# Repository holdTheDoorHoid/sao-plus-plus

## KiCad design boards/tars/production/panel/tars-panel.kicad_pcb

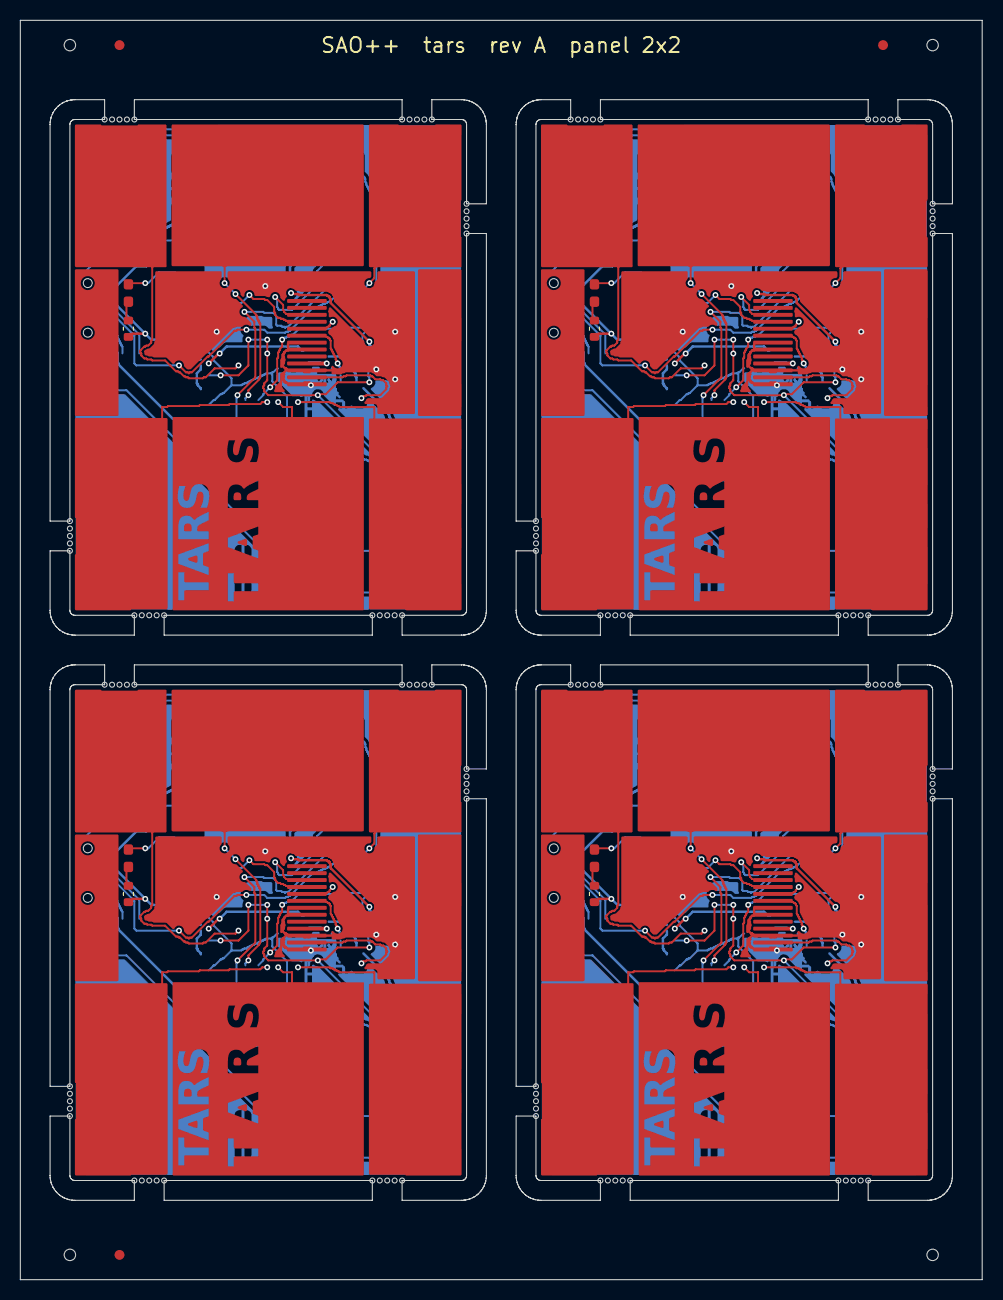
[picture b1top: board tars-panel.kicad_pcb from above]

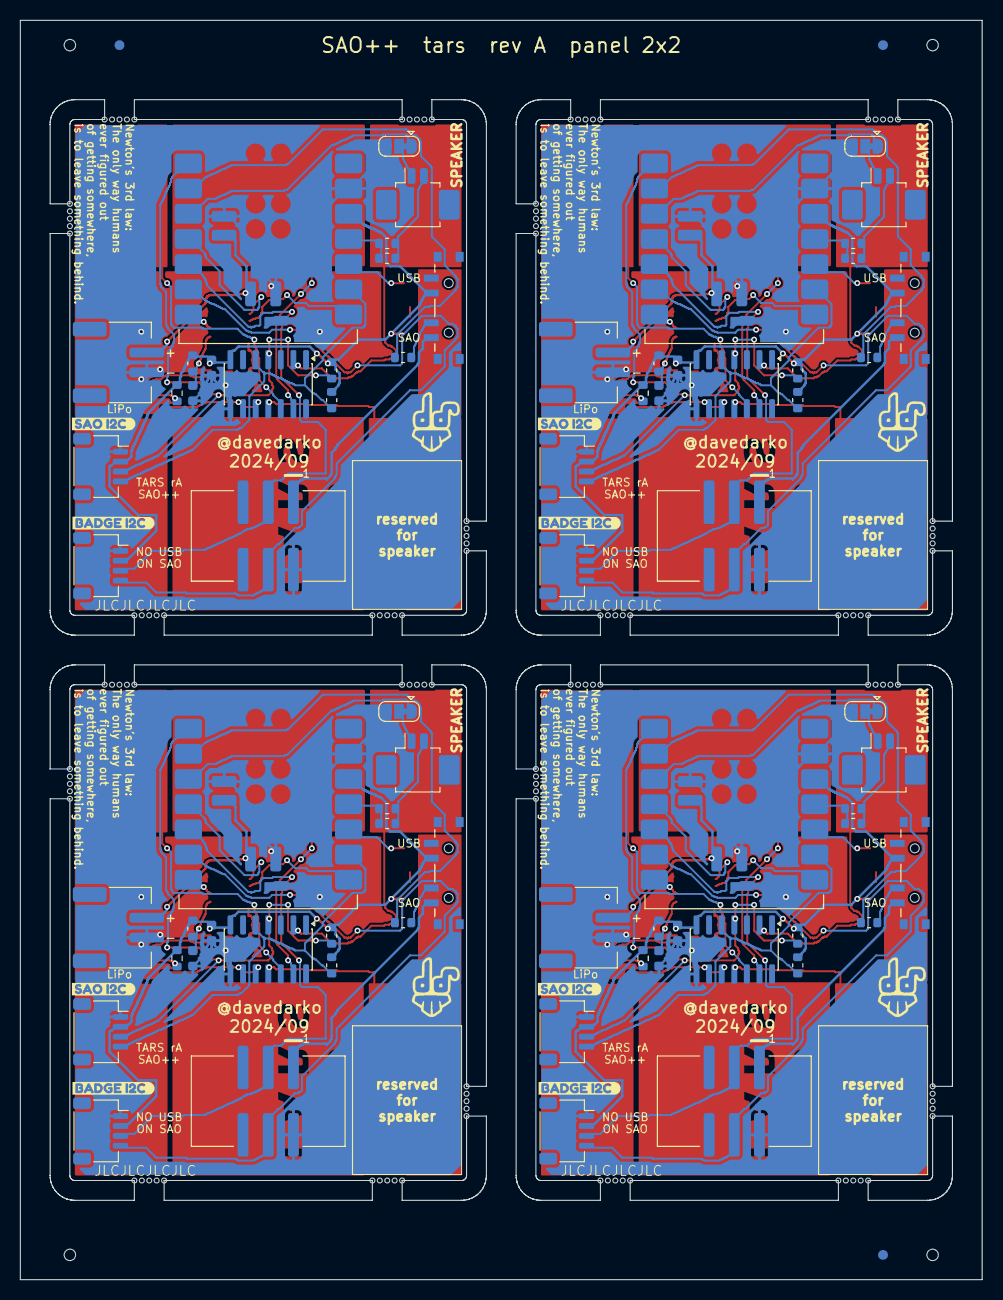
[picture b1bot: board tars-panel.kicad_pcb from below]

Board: 2 copper layers, 97.0 x 127.0 mm, 120 parts (84 on the bottom side), 108 nets.

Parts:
C101, C102, C201, C202, C301, C302, C401, C402: 100n; SAOPP_C_0603_1608Metric
D101, D201, D301, D401: red; LED_0603_1608Metric_Pad1.05x0.95mm_HandSolder
J101, J201, J301, J401: SAO v1.69bis; SAOPP_CONN-01_BoxHeader_2x03_P2.54mm_SMD_XFCN_BH254VS-6P
J102, J202, J302, J402: speaker; Molex_PicoBlade_53261-0271_1x02-1MP_P1.25mm_Horizontal
J103, J203, J303, J403: Qwiic: badge I2C; JST_SH_SM04B-SRSS-TB_1x04-1MP_P1.00mm_Horizontal
J104, J204, J304, J404: Qwiic: XIAO's own I2C; JST_SH_SM04B-SRSS-TB_1x04-1MP_P1.00mm_Horizontal
J105, J205, J305, J405: LiPo 3.7 V; SAOPP_CONN-10_JST_PH_S2B-PH-SM4-TB_1x02_Horizontal
JP101, JP201, JP301, JP401: speaker mode; SolderJumper-3_P1.3mm_Bridged12_RoundedPad1.0x1.5mm
R109, R209, R309, R409: 11; R_0603_1608Metric
R110, R111, R112, R116, R210, R211, R212, R216, R310, R311, R312, R316, R410, R411, R412, R416: 1.3k; SAOPP_R_0603_1608Metric
R113, R114, R115, R213, R214, R215, R313, R314, R315, R413, R414, R415: 330; SAOPP_R_0603_1608Metric
Ref**: Val**; davedarko_logo_silk_outline
Ref**#2, Ref**#3, Ref**#4: Val**; davedarko_logo_silk_outline
SW101, SW201, SW301, SW401: SAO / OFF / USB-BAT; SAOPP_SW-01_Slide_SP3T_CK_PCM13SMTR
TP101, TP201, TP301, TP401: touch A; TestPoint_Pad_D1.0mm
TP102, TP202, TP302, TP402: touch up; TestPoint_Pad_D1.0mm
TP103, TP203, TP303, TP403: touch B; TestPoint_Pad_D1.0mm
TP104, TP204, TP304, TP404: touch left; TestPoint_Pad_D1.0mm
TP105, TP205, TP305, TP405: touch down; TestPoint_Pad_D1.0mm
TP106, TP206, TP306, TP406: touch right; TestPoint_Pad_D1.0mm
U101, U201, U301, U401: ST7735S 80x160; ST7735S-160x80-13PIN
U102, U202, U302, U402: XIAO ESP32-C3 / S3 / C6; SAOPP_MCU-01_Seeed_XIAO_SMD_C3_S3_C6
U103, U203, U303, U403: CAP1206-1; SOIC-14_3.9x8.7mm_P1.27mm
kibuzzard-66F128E4, kibuzzard-66F128E4#2, kibuzzard-66F128E4#3, kibuzzard-66F128E4#4: G***; kibuzzard-66F128E4
kibuzzard-66F12846, kibuzzard-66F12846#2, kibuzzard-66F12846#3, kibuzzard-66F12846#4: G***; kibuzzard-66F12846

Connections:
B2-BAT+: J205.1, U202.15
B2-GND: C201.2, C202.2, J201.2, J203.1, J204.1, J205.2, JP201.3, U201.7, U201.8, U201.11, U201.13, U202.13, U202.16, U203.8
B2-LEDA: R209.2, U201.12
B2-LED_A: D201.2, R210.2
B2-LED_K: D201.1, U202.10
B2-OFF_SENSE: R213.2, U202.2
B2-OFF_SW: R213.1, SW201.2
B2-PRIV_SCL: J204.4, R212.2, U202.9, U203.5
B2-PRIV_SDA: J204.3, R211.2, U202.1, U203.4
B2-SCL: J201.4, J203.4, U202.6
B2-SDA: J201.3, J203.3, U202.5
B2-SPK_1: J202.1, JP201.2
B2-SPK_A: R214.1, R215.1, U202.11
B2-SPK_AR: J202.2, R214.2, R215.2
B2-SPK_B: JP201.1, U202.3
B2-TFT_DC: U201.5, U202.7
B2-TFT_MOSI: U201.3, U202.4
B2-TFT_RST: C201.1, R216.2, U201.6
B2-TFT_SCLK: U201.4, U202.8
B2-TOUCH_A: TP201.1, U203.2
B2-TOUCH_B: TP203.1, U203.12
B2-TOUCH_DOWN: TP205.1, U203.10
B2-TOUCH_LEFT: TP204.1, U203.11
B2-TOUCH_RIGHT: TP206.1, U203.9
B2-TOUCH_UP: TP202.1, U203.13
B2-V3V3: C202.1, J203.2, J204.2, R209.1, R210.1, R211.1, R212.1, R216.1, SW201.3, U201.10, U202.12, U203.7
B2-VSAO: J201.1, SW201.1
B3-BAT+: J305.1, U302.15
B3-GND: C301.2, C302.2, J301.2, J303.1, J304.1, J305.2, JP301.3, U301.7, U301.8, U301.11, U301.13, U302.13, U302.16, U303.8
B3-LEDA: R309.2, U301.12
B3-LED_A: D301.2, R310.2
B3-LED_K: D301.1, U302.10
B3-OFF_SENSE: R313.2, U302.2
B3-OFF_SW: R313.1, SW301.2
B3-PRIV_SCL: J304.4, R312.2, U302.9, U303.5
B3-PRIV_SDA: J304.3, R311.2, U302.1, U303.4
B3-SCL: J301.4, J303.4, U302.6
B3-SDA: J301.3, J303.3, U302.5
B3-SPK_1: J302.1, JP301.2
B3-SPK_A: R314.1, R315.1, U302.11
B3-SPK_AR: J302.2, R314.2, R315.2
B3-SPK_B: JP301.1, U302.3
B3-TFT_DC: U301.5, U302.7
B3-TFT_MOSI: U301.3, U302.4
B3-TFT_RST: C301.1, R316.2, U301.6
B3-TFT_SCLK: U301.4, U302.8
B3-TOUCH_A: TP301.1, U303.2
B3-TOUCH_B: TP303.1, U303.12
B3-TOUCH_DOWN: TP305.1, U303.10
B3-TOUCH_LEFT: TP304.1, U303.11
B3-TOUCH_RIGHT: TP306.1, U303.9
B3-TOUCH_UP: TP302.1, U303.13
B3-V3V3: C302.1, J303.2, J304.2, R309.1, R310.1, R311.1, R312.1, R316.1, SW301.3, U301.10, U302.12, U303.7
B3-VSAO: J301.1, SW301.1
B4-BAT+: J405.1, U402.15
B4-GND: C401.2, C402.2, J401.2, J403.1, J404.1, J405.2, JP401.3, U401.7, U401.8, U401.11, U401.13, U402.13, U402.16, U403.8
B4-LEDA: R409.2, U401.12
B4-LED_A: D401.2, R410.2
B4-LED_K: D401.1, U402.10
B4-OFF_SENSE: R413.2, U402.2
B4-OFF_SW: R413.1, SW401.2
B4-PRIV_SCL: J404.4, R412.2, U402.9, U403.5
B4-PRIV_SDA: J404.3, R411.2, U402.1, U403.4
B4-SCL: J401.4, J403.4, U402.6
B4-SDA: J401.3, J403.3, U402.5
B4-SPK_1: J402.1, JP401.2
B4-SPK_A: R414.1, R415.1, U402.11
B4-SPK_AR: J402.2, R414.2, R415.2
B4-SPK_B: JP401.1, U402.3
B4-TFT_DC: U401.5, U402.7
B4-TFT_MOSI: U401.3, U402.4
B4-TFT_RST: C401.1, R416.2, U401.6
B4-TFT_SCLK: U401.4, U402.8
B4-TOUCH_A: TP401.1, U403.2
B4-TOUCH_B: TP403.1, U403.12
B4-TOUCH_DOWN: TP405.1, U403.10
B4-TOUCH_LEFT: TP404.1, U403.11
B4-TOUCH_RIGHT: TP406.1, U403.9
B4-TOUCH_UP: TP402.1, U403.13
B4-V3V3: C402.1, J403.2, J404.2, R409.1, R410.1, R411.1, R412.1, R416.1, SW401.3, U401.10, U402.12, U403.7
B4-VSAO: J401.1, SW401.1
BAT+: J105.1, U102.15
GND: C101.2, C102.2, J101.2, J103.1, J104.1, J105.2, JP101.3, U101.7, U101.8, U101.11, U101.13, U102.13, U102.16, U103.8
LEDA: R109.2, U101.12
LED_A: D101.2, R110.2
LED_K: D101.1, U102.10
OFF_SENSE: R113.2, U102.2
OFF_SW: R113.1, SW101.2
PRIV_SCL: J104.4, R112.2, U102.9, U103.5
PRIV_SDA: J104.3, R111.2, U102.1, U103.4
SCL: J101.4, J103.4, U102.6
SDA: J101.3, J103.3, U102.5
SPK_1: J102.1, JP101.2
SPK_A: R114.1, R115.1, U102.11
SPK_AR: J102.2, R114.2, R115.2
SPK_B: JP101.1, U102.3
TFT_DC: U101.5, U102.7
TFT_MOSI: U101.3, U102.4
TFT_RST: C101.1, R116.2, U101.6
TFT_SCLK: U101.4, U102.8
TOUCH_A: TP101.1, U103.2
TOUCH_B: TP103.1, U103.12
TOUCH_DOWN: TP105.1, U103.10
TOUCH_LEFT: TP104.1, U103.11
TOUCH_RIGHT: TP106.1, U103.9
TOUCH_UP: TP102.1, U103.13
V3V3: C102.1, J103.2, J104.2, R109.1, R110.1, R111.1, R112.1, R116.1, SW101.3, U101.10, U102.12, U103.7
VSAO: J101.1, SW101.1

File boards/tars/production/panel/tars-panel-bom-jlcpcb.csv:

Comment,Designator,Footprint,LCSC Part #
100n,"C101,C102,C201,C202,C301,C302,C401,C402",SAOPP_C_0603_1608Metric,C14663
red,"D101,D201,D301,D401",LED_0603_1608Metric_Pad1.05x0.95mm_HandSolder,C125099
SAO v1.69bis,"J101,J201,J301,J401",SAOPP_CONN-01_BoxHeader_2x03_P2.54mm_SMD_XFCN_BH254VS-6P,C492445
speaker,"J102,J202,J302,J402",Molex_PicoBlade_53261-0271_1x02-1MP_P1.25mm_Horizontal,C177225
Qwiic: badge I2C,"J103,J203,J303,J403",JST_SH_SM04B-SRSS-TB_1x04-1MP_P1.00mm_Horizontal,C160404
Qwiic: XIAO's own I2C,"J104,J204,J304,J404",JST_SH_SM04B-SRSS-TB_1x04-1MP_P1.00mm_Horizontal,C160404
LiPo 3.7 V,"J105,J205,J305,J405",SAOPP_CONN-10_JST_PH_S2B-PH-SM4-TB_1x02_Horizontal,C295747
11,"R109,R209,R309,R409",R_0603_1608Metric,
1.3k,"R111,R112,R116,R211,R212,R216,R311,R312,R316,R411,R412,R416,R110,R210,R310,R410",SAOPP_R_0603_1608Metric,C22767
330,"R113,R114,R115,R213,R214,R215,R313,R314,R315,R413,R414,R415",SAOPP_R_0603_1608Metric,C23138
SAO / OFF / USB-BAT,"SW101,SW201,SW301,SW401",SAOPP_SW-01_Slide_SP3T_CK_PCM13SMTR,C221842
ST7735S 80x160,"U101,U201,U301,U401",ST7735S-160x80-13PIN,
XIAO ESP32-C3 / S3 / C6,"U102,U202,U302,U402",SAOPP_MCU-01_Seeed_XIAO_SMD_C3_S3_C6,
CAP1206-1,"U103,U203,U303,U403",SOIC-14_3.9x8.7mm_P1.27mm,C2652106

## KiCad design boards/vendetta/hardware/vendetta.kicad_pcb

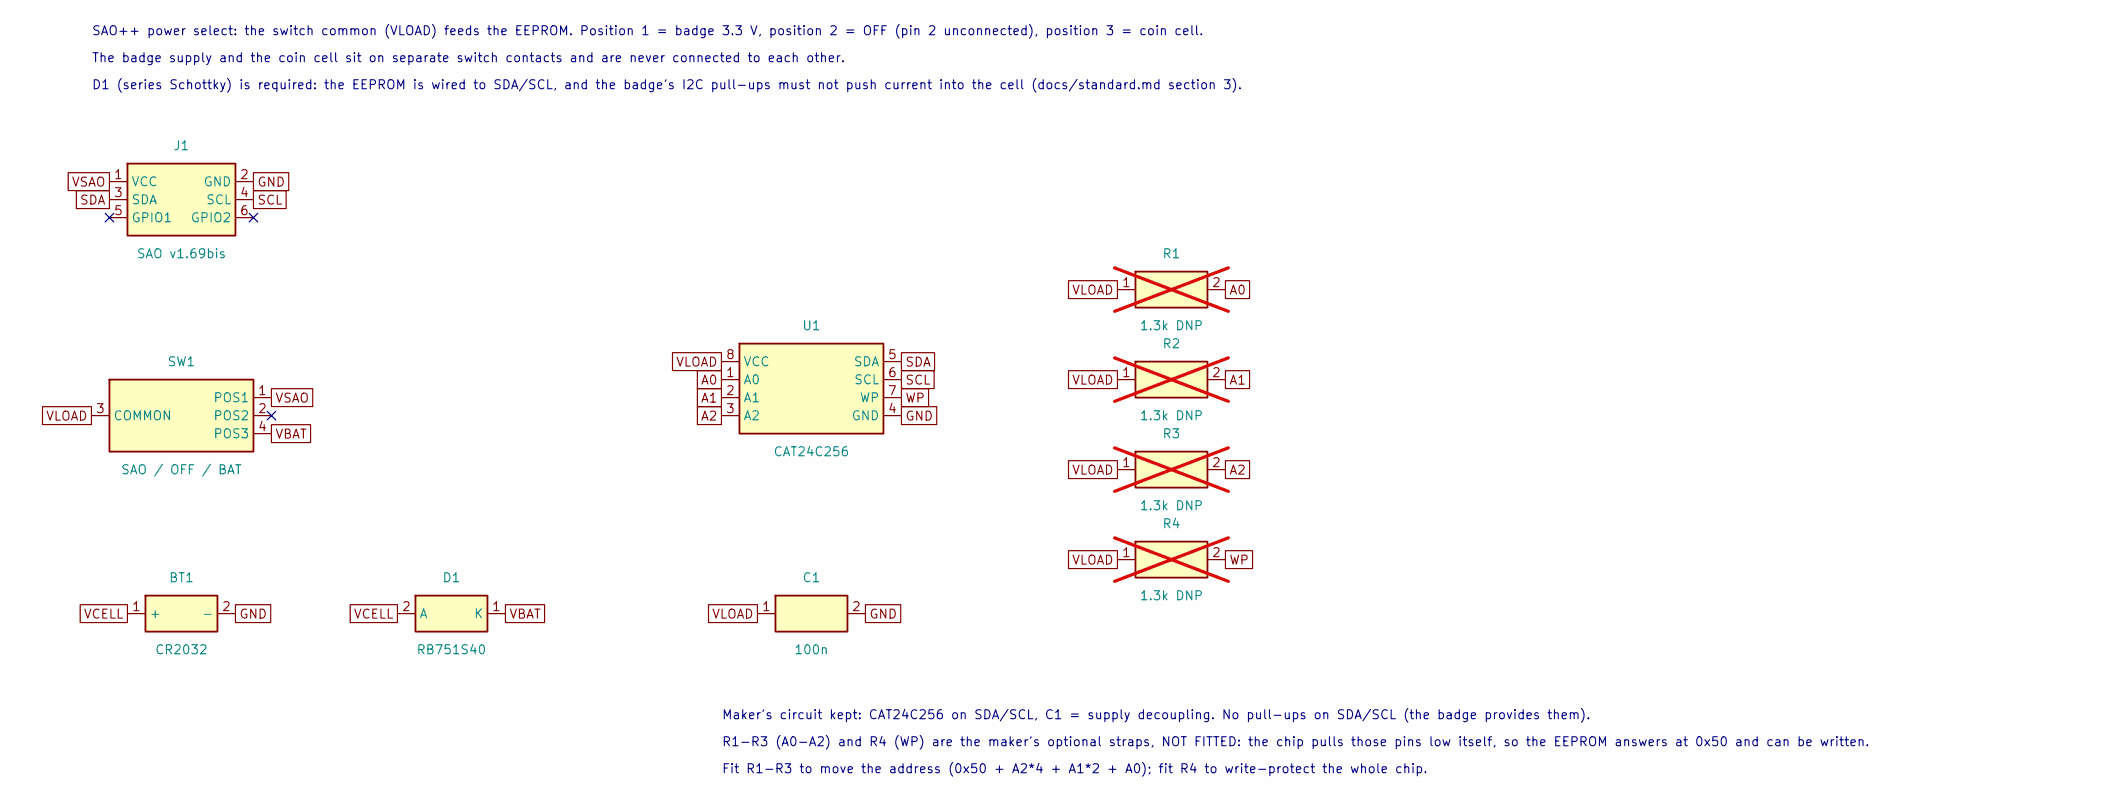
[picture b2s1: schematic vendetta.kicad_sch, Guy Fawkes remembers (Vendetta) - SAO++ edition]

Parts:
BT1: CR2032; SAOPP_BAT-01_CR2032_SMD_TE_BAT-HLD-001; MPN BAT-HLD-001; LCSC C7501066
C1: 100n; SAOPP_C_0603_1608Metric; MPN CC0603KRX7R9BB104; LCSC C14663
D1: RB751S40; D_SOD-523; MPN RB751S40T1G; LCSC C232576
J1: SAO v1.69bis; SAOPP_CONN-01_BoxHeader_2x03_P2.54mm_SMD_XFCN_BH254VS-6P; MPN BH254VS-6P; LCSC C492445
R1, R2, R3, R4: 1.3k DNP; SAOPP_R_0603_1608Metric; MPN 0603WAF1301T5E; LCSC C22767; not fitted
SW1: SAO / OFF / BAT; SAOPP_SW-01_Slide_SP3T_CK_PCM13SMTR; MPN PCM13SMTR; LCSC C221842
U1: CAT24C256; SOIC-8_5.3x5.3mm_P1.27mm; MPN CAT24C256XI-T2

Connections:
A0: R1.2, U1.1 (A0)
A1: R2.2, U1.2 (A1)
A2: R3.2, U1.3 (A2)
GND: BT1.2 (-), C1.2, J1.2 (GND), U1.4 (GND)
SCL: J1.4 (SCL), U1.6 (SCL)
SDA: J1.3 (SDA), U1.5 (SDA)
VBAT: D1.1 (K), SW1.4 (POS3)
VCELL: BT1.1 (+), D1.2 (A)
VLOAD: C1.1, R1.1, R2.1, R3.1, R4.1, SW1.3 (COMMON), U1.8 (VCC)
VSAO: J1.1 (VCC), SW1.1 (POS1)
WP: R4.2, U1.7 (WP)

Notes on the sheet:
SAO++ power select: the switch common (VLOAD) feeds the EEPROM. Position 1 = badge 3.3 V, position 2 = OFF (pin 2 unconnected), position 3 = coin cell.
The badge supply and the coin cell sit on separate switch contacts and are never connected to each other.
D1 (series Schottky) is required: the EEPROM is wired to SDA/SCL, and the badge's I2C pull-ups must not push current into the cell (docs/standard.md section 3).
Maker's circuit kept: CAT24C256 on SDA/SCL, C1 = supply decoupling. No pull-ups on SDA/SCL (the badge provides them).
R1-R3 (A0-A2) and R4 (WP) are the maker's optional straps, NOT FITTED: the chip pulls those pins low itself, so the EEPROM answers at 0x50 and can be written.
Fit R1-R3 to move the address (0x50 + A2*4 + A1*2 + A0); fit R4 to write-protect the whole chip.

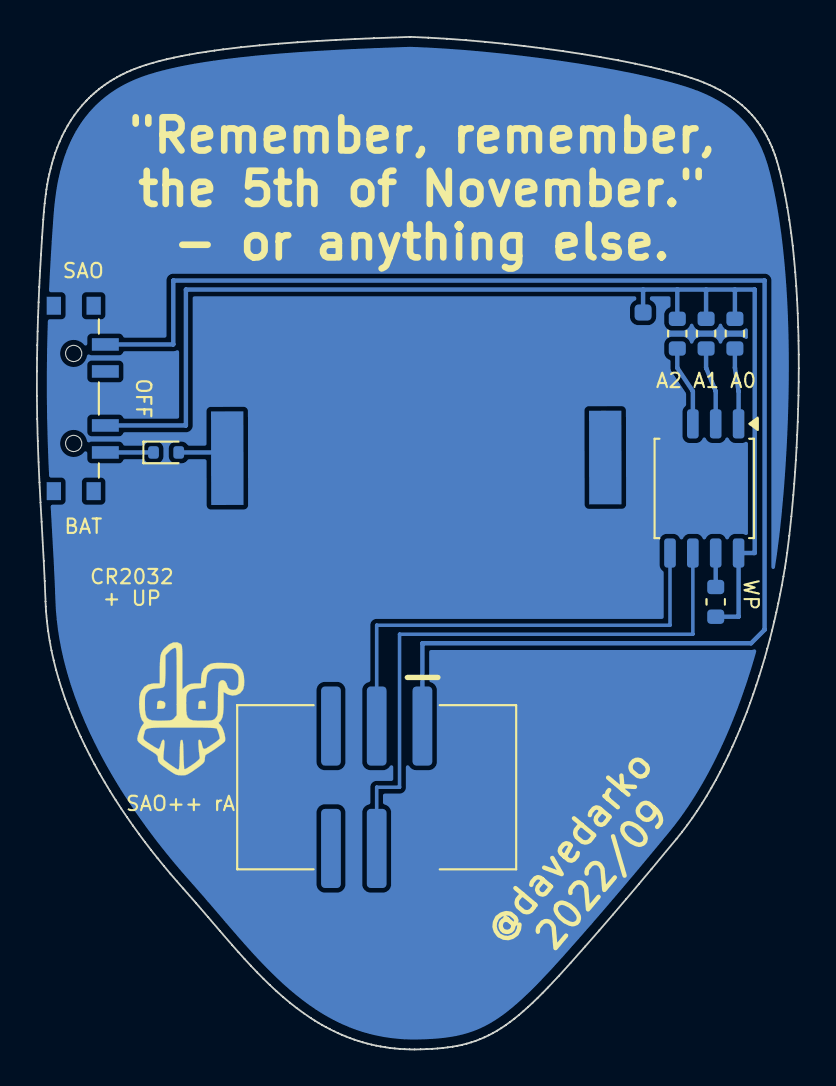
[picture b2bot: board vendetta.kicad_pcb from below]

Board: 2 copper layers, 42.3 x 56.3 mm, 12 parts (11 on the bottom side), 11 nets.

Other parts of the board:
Ref**: Val**; vendettaSAO
Ref**#2: Val**; davedarko_logo_silk_outline

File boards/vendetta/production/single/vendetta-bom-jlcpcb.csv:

Comment,Designator,Footprint,LCSC Part #
CR2032,BT1,SAOPP_BAT-01_CR2032_SMD_TE_BAT-HLD-001,C7501066
100n,C1,SAOPP_C_0603_1608Metric,C14663
RB751S40,D1,D_SOD-523,C232576
SAO v1.69bis,J1,SAOPP_CONN-01_BoxHeader_2x03_P2.54mm_SMD_XFCN_BH254VS-6P,C492445
SAO / OFF / BAT,SW1,SAOPP_SW-01_Slide_SP3T_CK_PCM13SMTR,C221842
CAT24C256,U1,SOIC-8_5.3x5.3mm_P1.27mm,

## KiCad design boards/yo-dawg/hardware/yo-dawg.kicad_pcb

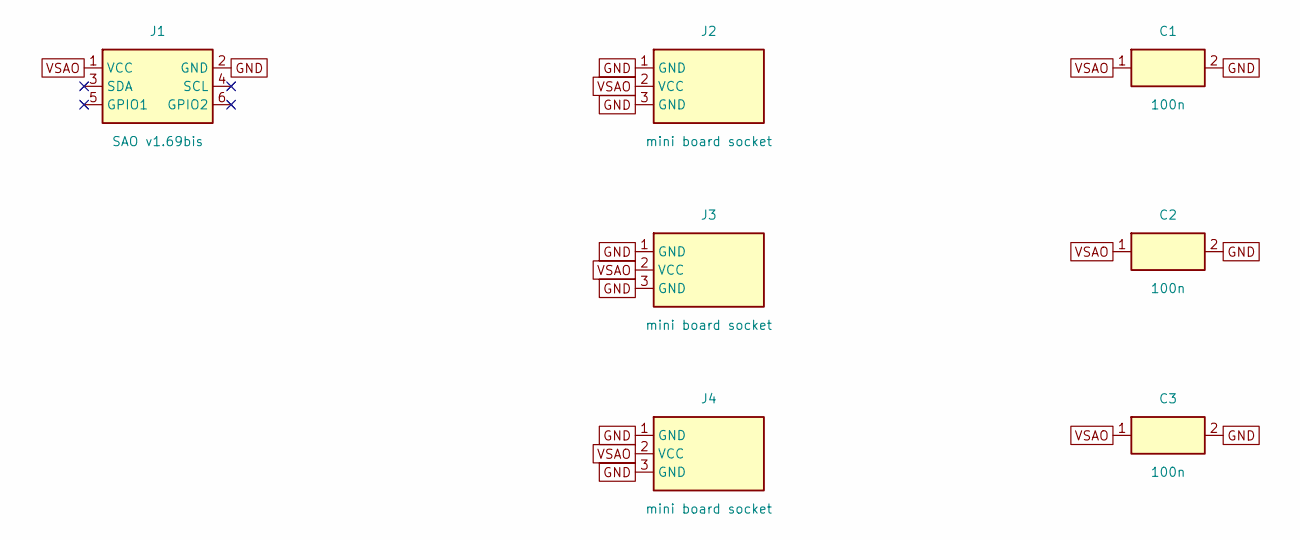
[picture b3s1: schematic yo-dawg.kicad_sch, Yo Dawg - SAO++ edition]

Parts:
C1, C2, C3: 100n; SAOPP_C_0603_1608Metric; MPN CC0603KRX7R9BB104; LCSC C14663
J1: SAO v1.69bis; SAOPP_CONN-01_BoxHeader_2x03_P2.54mm_SMD_XFCN_BH254VS-6P; MPN BH254VS-6P; LCSC C492445
J2, J3, J4: mini board socket; PinSocket_1x03_P1.27mm_Vertical; MPN not chosen: 1x3 female socket strip, 1.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

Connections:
GND: C1.2, C2.2, C3.2, J1.2 (GND), J2.1 (GND), J2.3 (GND), J3.1 (GND), J3.3 (GND), J4.1 (GND), J4.3 (GND)
VSAO: C1.1, C2.1, C3.1, J1.1 (VCC), J2.2 (VCC), J3.2 (VCC), J4.2 (VCC)

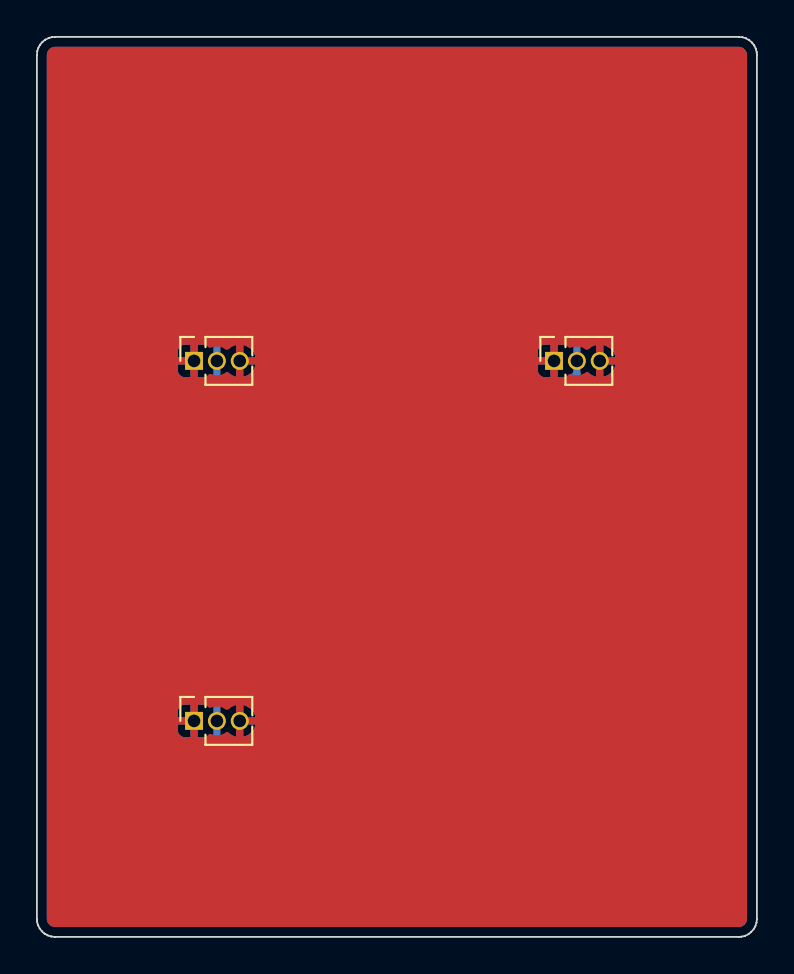
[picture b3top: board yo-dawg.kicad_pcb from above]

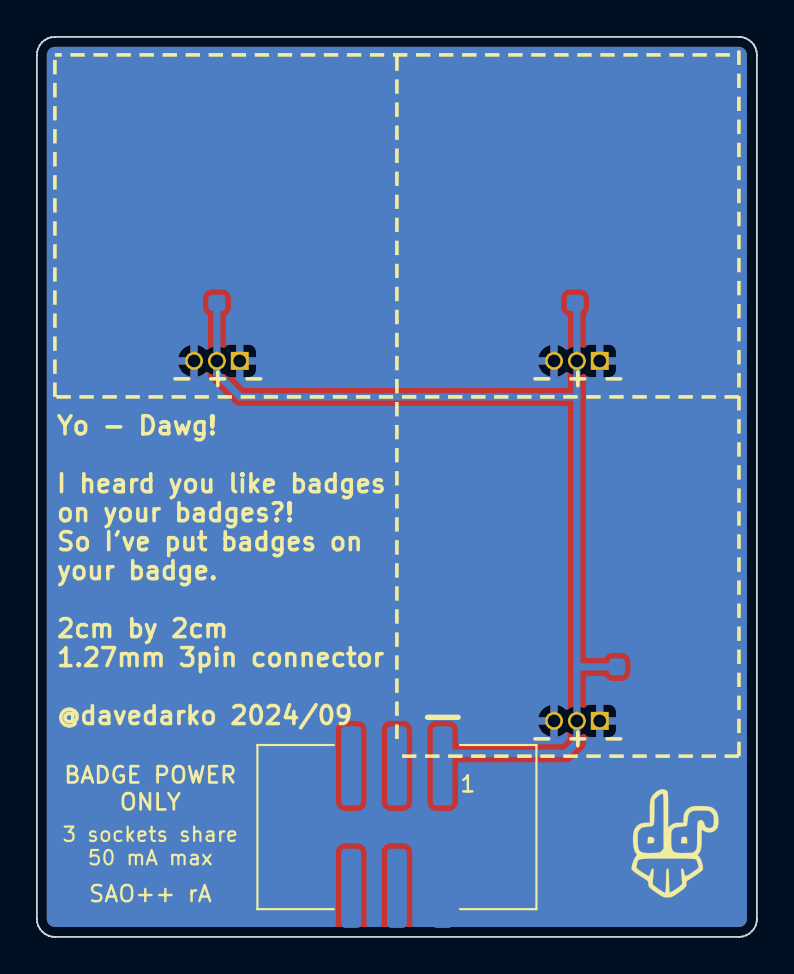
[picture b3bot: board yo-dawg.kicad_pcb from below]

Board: 2 copper layers, 40.0 x 50.0 mm, 8 parts (5 on the bottom side), 2 nets.

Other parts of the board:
Ref**: Val**; davedarko_logo_silk_outline

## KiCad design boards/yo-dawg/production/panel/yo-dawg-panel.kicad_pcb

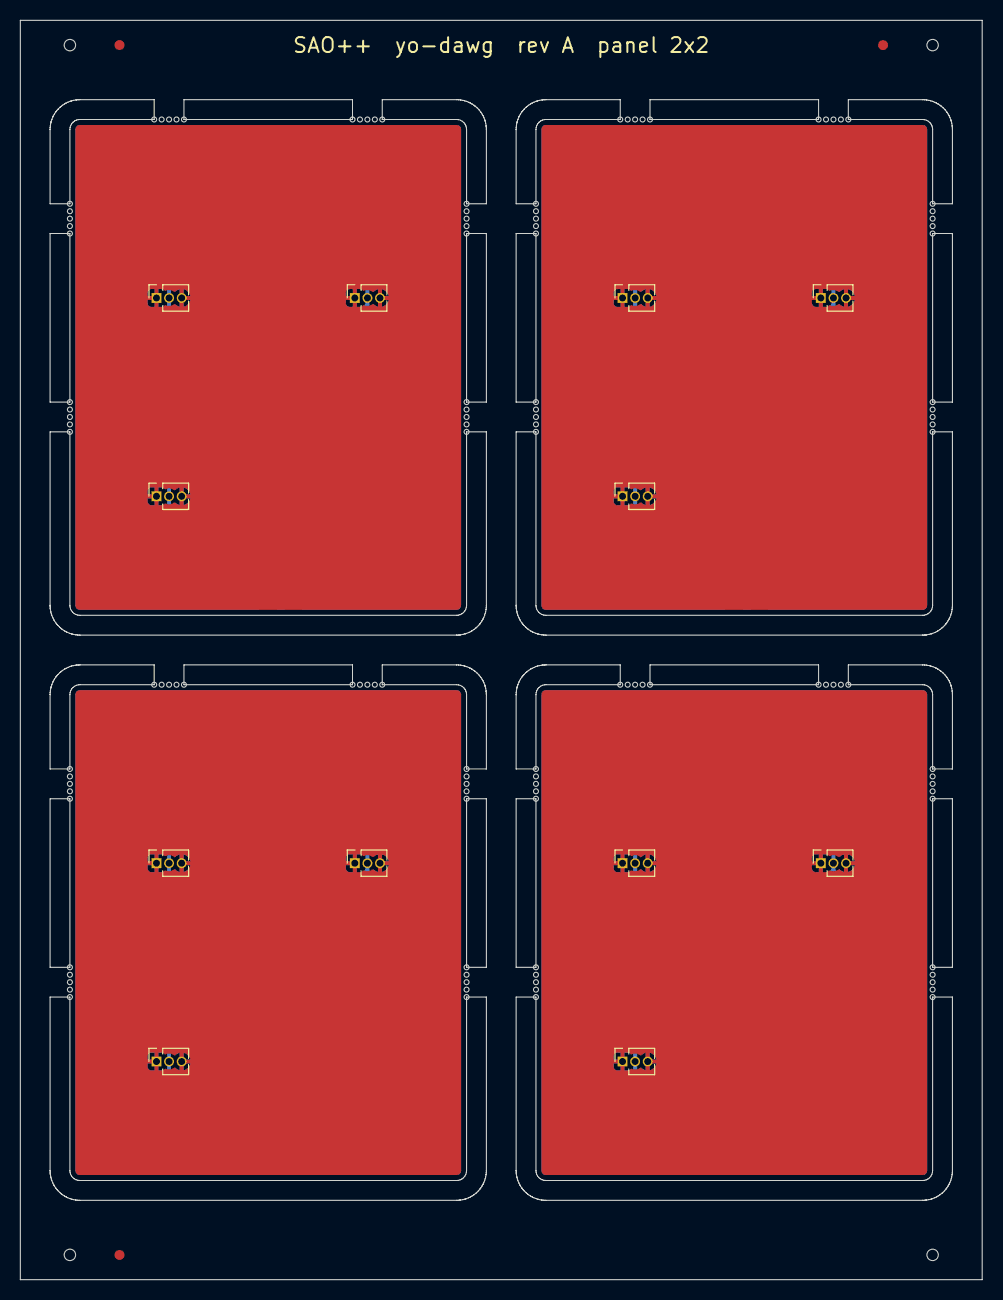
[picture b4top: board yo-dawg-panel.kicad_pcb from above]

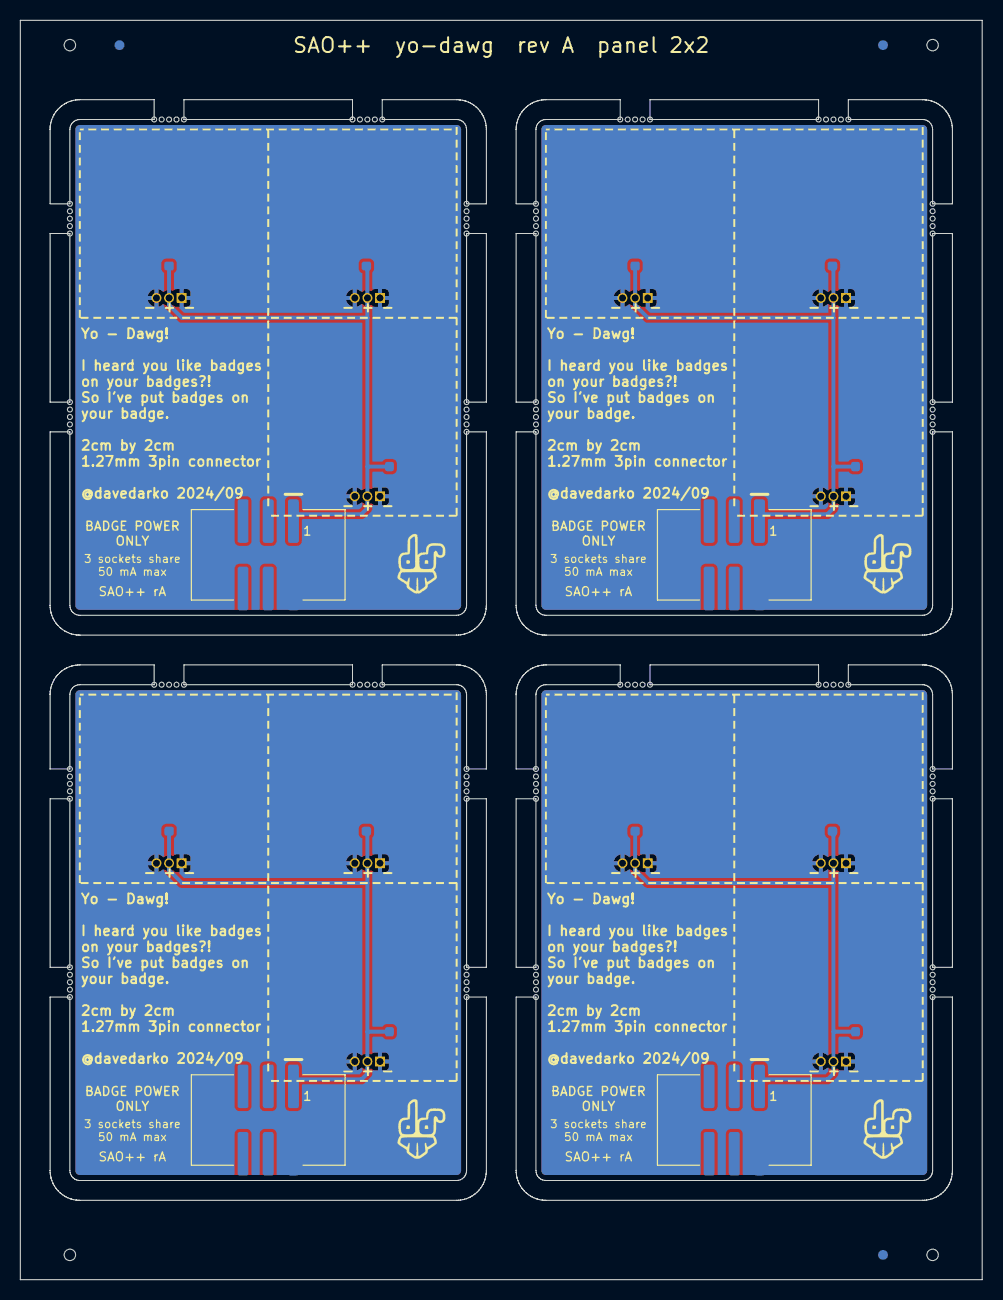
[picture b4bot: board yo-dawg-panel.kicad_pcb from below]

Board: 2 copper layers, 97.0 x 127.0 mm, 32 parts (20 on the bottom side), 8 nets.

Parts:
C101, C102, C103, C201, C202, C203, C301, C302, C303, C401, C402, C403: 100n; SAOPP_C_0603_1608Metric
J101, J201, J301, J401: SAO v1.69bis; SAOPP_CONN-01_BoxHeader_2x03_P2.54mm_SMD_XFCN_BH254VS-6P
J102, J103, J104, J202, J203, J204, J302, J303, J304, J402, J403, J404: mini board socket; PinSocket_1x03_P1.27mm_Vertical
Ref**: Val**; davedarko_logo_silk_outline
Ref**#2, Ref**#3, Ref**#4: Val**; davedarko_logo_silk_outline

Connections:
B2-GND: C201.2, C202.2, C203.2, J201.2, J202.1, J202.3, J203.1, J203.3, J204.1, J204.3
B2-VSAO: C201.1, C202.1, C203.1, J201.1, J202.2, J203.2, J204.2
B3-GND: C301.2, C302.2, C303.2, J301.2, J302.1, J302.3, J303.1, J303.3, J304.1, J304.3
B3-VSAO: C301.1, C302.1, C303.1, J301.1, J302.2, J303.2, J304.2
B4-GND: C401.2, C402.2, C403.2, J401.2, J402.1, J402.3, J403.1, J403.3, J404.1, J404.3
B4-VSAO: C401.1, C402.1, C403.1, J401.1, J402.2, J403.2, J404.2
GND: C101.2, C102.2, C103.2, J101.2, J102.1, J102.3, J103.1, J103.3, J104.1, J104.3
VSAO: C101.1, C102.1, C103.1, J101.1, J102.2, J103.2, J104.2

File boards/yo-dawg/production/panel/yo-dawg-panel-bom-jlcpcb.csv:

Comment,Designator,Footprint,LCSC Part #
100n,"C101,C102,C103,C201,C202,C203,C301,C302,C303,C401,C402,C403",SAOPP_C_0603_1608Metric,C14663
SAO v1.69bis,"J101,J201,J301,J401",SAOPP_CONN-01_BoxHeader_2x03_P2.54mm_SMD_XFCN_BH254VS-6P,C492445
mini board socket,"J102,J103,J104,J202,J203,J204,J302,J303,J304,J402,J403,J404",PinSocket_1x03_P1.27mm_Vertical,
